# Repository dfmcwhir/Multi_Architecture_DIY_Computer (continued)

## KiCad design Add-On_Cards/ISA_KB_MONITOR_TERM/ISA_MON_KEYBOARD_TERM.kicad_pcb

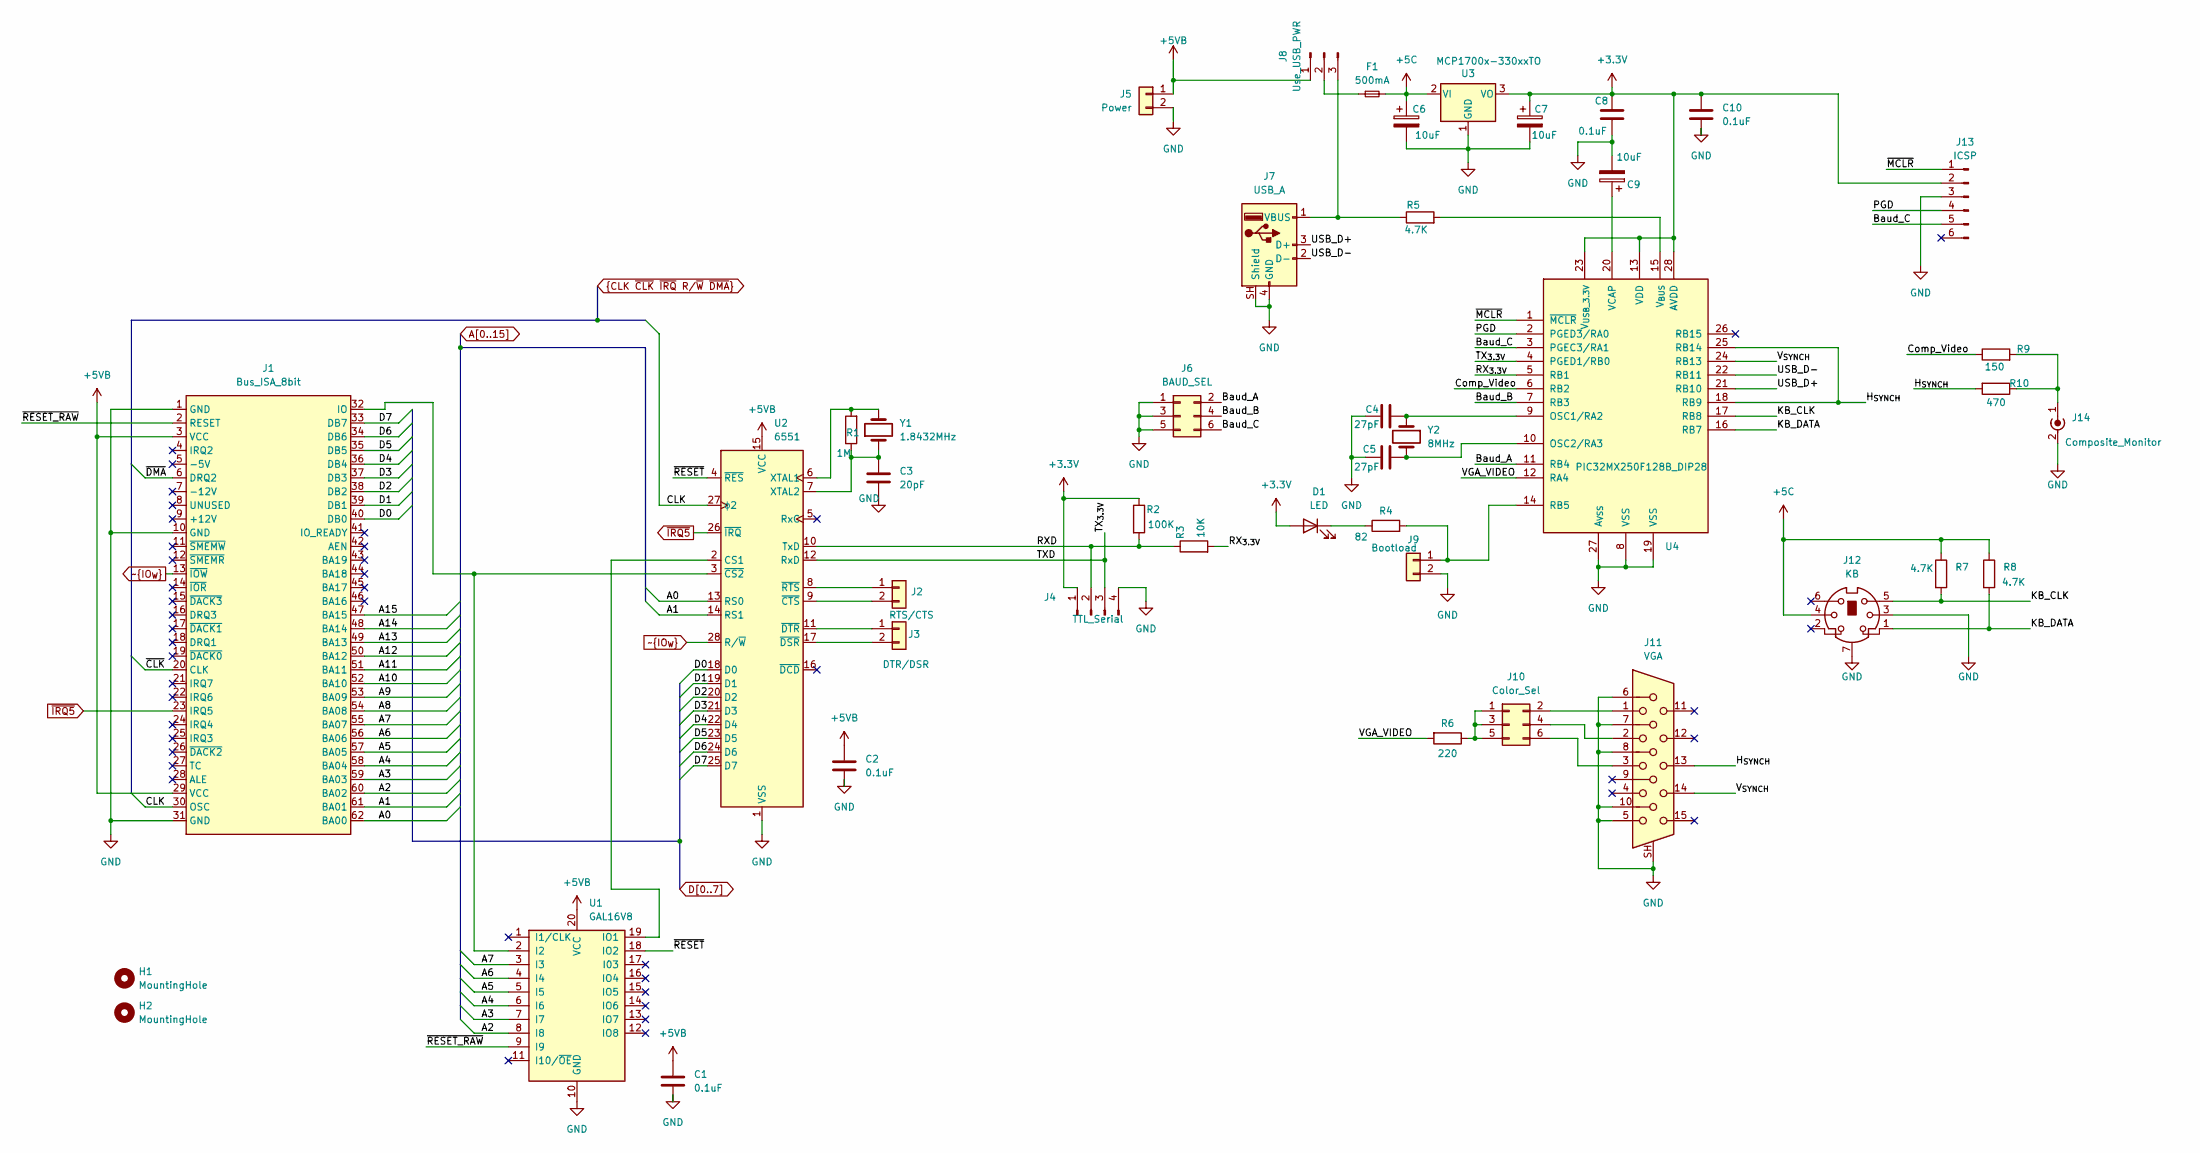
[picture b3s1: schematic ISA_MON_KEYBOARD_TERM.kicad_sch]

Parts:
C1, C2, C8, C10: 0.1uF; C_Disc_D4.7mm_W2.5mm_P5.00mm
C3: 20pF; C_Disc_D4.7mm_W2.5mm_P5.00mm
C4, C5: 27pF; C_Disc_D4.7mm_W2.5mm_P5.00mm
C6, C7, C9: 10uF; CP_Radial_D5.0mm_P2.50mm
D1: LED; LED_D5.0mm
F1: 500mA; R_Axial_DIN0207_L6.3mm_D2.5mm_P10.16mm_Horizontal
H1, H2: MountingHole; MountingHole_3.2mm_M3
J1: Bus_ISA_8bit; BUS_8-bit_ISA
J2: RTS/CTS; PinHeader_1x02_P2.54mm_Vertical
J3: DTR/DSR; PinHeader_1x02_P2.54mm_Vertical
J4: TTL_Serial; PinHeader_1x04_P2.54mm_Vertical
J5: Power; PinHeader_1x02_P2.54mm_Vertical
J6: BAUD_SEL; PinHeader_2x03_P2.54mm_Vertical
J7: USB_A; USB_A_Connfly_DS1095
J8: Use_USB_PWR; PinHeader_1x03_P2.54mm_Vertical
J9: Bootload; PinHeader_1x02_P2.54mm_Vertical
J10: Color_Sel; PinHeader_2x03_P2.54mm_Vertical
J11: VGA; DSUB-15-HD_Socket_Horizontal_P2.29x1.90mm_EdgePinOffset3.03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
J12: KB; Connector_Mini-DIN_Female_6Pin_2rows
J13: ICSP; PinHeader_1x06_P2.54mm_Vertical
J14: Composite_Monitor; RCA_JACK_Right_Angle_AliExpress
R1: 1M; R_Axial_DIN0207_L6.3mm_D2.5mm_P10.16mm_Horizontal
R2: 100K; R_Axial_DIN0207_L6.3mm_D2.5mm_P10.16mm_Horizontal
R3: 10K; R_Axial_DIN0207_L6.3mm_D2.5mm_P10.16mm_Horizontal
R4: 82; R_Axial_DIN0207_L6.3mm_D2.5mm_P10.16mm_Horizontal
R5, R7, R8: 4.7K; R_Axial_DIN0207_L6.3mm_D2.5mm_P10.16mm_Horizontal
R6: 220; R_Axial_DIN0207_L6.3mm_D2.5mm_P10.16mm_Horizontal
R9: 150; R_Axial_DIN0207_L6.3mm_D2.5mm_P10.16mm_Horizontal
R10: 470; R_Axial_DIN0207_L6.3mm_D2.5mm_P10.16mm_Horizontal
U1: GAL16V8; DIP-20_W7.62mm
U2: 6551; DIP-28_W15.24mm
U3: MCP1700x-330xxTO; TO-92_Wide
U4: PIC32MX250F128B_DIP28; DIP-28_W7.62mm
Y1: 1.8432MHz; Crystal_HC18-U_Vertical
Y2: 8MHz; Crystal_HC18-U_Vertical

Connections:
+3.3V: C7.1, C8.1, C10.1, D1.2 (A), J4.1, J13.2, R2.1, U3.3 (VO), U4.13 (VDD), U4.23 (V_{USB_3.3V}), U4.28 (AVDD)
+5C: C6.1, F1.2, J12.4, R7.1, R8.1, U3.2 (VI)
+5VB: C1.1, C2.1, J1.3 (VCC), J1.29 (VCC), J5.1, J8.1, U1.20 (VCC), U2.15 (VCC)
/Baud_A: J6.2, U4.11 (RB4)
/Baud_B: J6.4, U4.7 (RB3)
/Baud_C: J6.6, J13.5, U4.3 (PGEC3/RA1)
/Comp_Video: R9.1, U4.6 (RB2)
/H_{SYNCH}: J11.13, R10.2, U4.18 (RB9), U4.25 (RB14)
/KB_CLK: J12.5, R7.2, U4.17 (RB8)
/KB_DATA: J12.1, R8.2, U4.16 (RB7)
/PGD: J13.4, U4.2 (PGED3/RA0)
/RXD: J4.2, R2.2, R3.1, U2.10 (TxD)
/RX_{3.3V}: R3.2, U4.5 (RB1)
/TXD: J4.3, U2.12 (RxD), U4.4 (PGED1/RB0)
/USB_D+: J7.3 (D+), U4.21 (RB10)
/USB_D-: J7.2 (D-), U4.22 (RB11)
/VGA_VIDEO: R6.2, U4.12 (RA4)
/V_{SYNCH}: J11.14, U4.24 (RB13)
/~MCLR: J13.1, U4.1 (~MCLR)
/~RESET_RAW: J1.2 (RESET), U1.9 (I9)
/~RESET: U1.18 (IO2), U2.4 (~RES)
A0: J1.62 (BA00), U2.13 (RS0)
A1: J1.61 (BA01), U2.14 (RS1)
A2: J1.60 (BA02), U1.8 (I8)
A3: J1.59 (BA03), U1.7 (I7)
A4: J1.58 (BA04), U1.6 (I6)
A5: J1.57 (BA05), U1.5 (I5)
A6: J1.56 (BA06), U1.4 (I4)
A7: J1.55 (BA07), U1.3 (I3)
A8: J1.54 (BA08)
A9: J1.53 (BA09)
A10: J1.52 (BA10)
A11: J1.51 (BA11)
A12: J1.50 (BA12)
A13: J1.49 (BA13)
A14: J1.48 (BA14)
A15: J1.47 (BA15)
CLK: J1.30 (OSC), U2.27 (ϕ2)
D0: J1.40 (DB0), U2.18 (D0)
D1: J1.39 (DB1), U2.19 (D1)
D2: J1.38 (DB2), U2.20 (D2)
D3: J1.37 (DB3), U2.21 (D3)
D4: J1.36 (DB4), U2.22 (D4)
D5: J1.35 (DB5), U2.23 (D5)
D6: J1.34 (DB6), U2.24 (D6)
D7: J1.33 (DB7), U2.25 (D7)
GND: C1.2, C2.2, C3.2, C4.2, C5.2, C6.2, C7.2, C8.2, C9.2, C10.2, J1.1 (GND), J1.10 (GND), J1.31 (GND), J4.4, J5.2, J6.1, J6.3, J6.5, J7.4 (GND), J7.SH (Shield), J9.2, J11.5, J11.6, J11.7, J11.8, J11.10, J11.SH, J12.3, J12.7, J13.3, J14.2 (Ext), U1.10 (GND), U2.1 (VSS), U3.1 (GND), U4.8 (VSS), U4.19 (VSS), U4.27 (A_{VSS})
unnamed: D1.1 (K), R4.1
unnamed: J1.32 (IO), U1.2 (I2), U2.3 (~CS2)
unnamed: J2.1, U2.8 (~RTS)
unnamed: J2.2, U2.9 (~CTS)
unnamed: J3.1, U2.11 (~DTR)
unnamed: J3.2, U2.17 (~DSR)
unnamed: J7.1 (VBUS), J8.3, R5.1
unnamed: F1.1, J8.2
unnamed: J9.1, R4.2, U4.14 (RB5)
unnamed: J10.1, J10.3, J10.5, R6.1
unnamed: J10.2, J11.1
unnamed: J10.4, J11.2
unnamed: J10.6, J11.3
unnamed: J14.1 (In), R9.2, R10.1
unnamed: U1.19 (IO1), U2.2 (CS1)
unnamed: R1.2, U2.6 (XTAL1), Y1.2
unnamed: C3.1, R1.1, U2.7 (XTAL2), Y1.1
unnamed: C4.1, U4.9 (OSC1/RA2), Y2.1
unnamed: C5.1, U4.10 (OSC2/RA3), Y2.2
unnamed: C9.1, U4.20 (VCAP)
unnamed: R5.2, U4.15 (V_{BUS})
~CLK: J1.20 (CLK)
~DMA: J1.6 (DRQ2)
~IO_{W}: J1.13 (~IOW), U2.28 (R/~W)
~IRQ5: J1.23 (IRQ5), U2.26 (~IRQ)

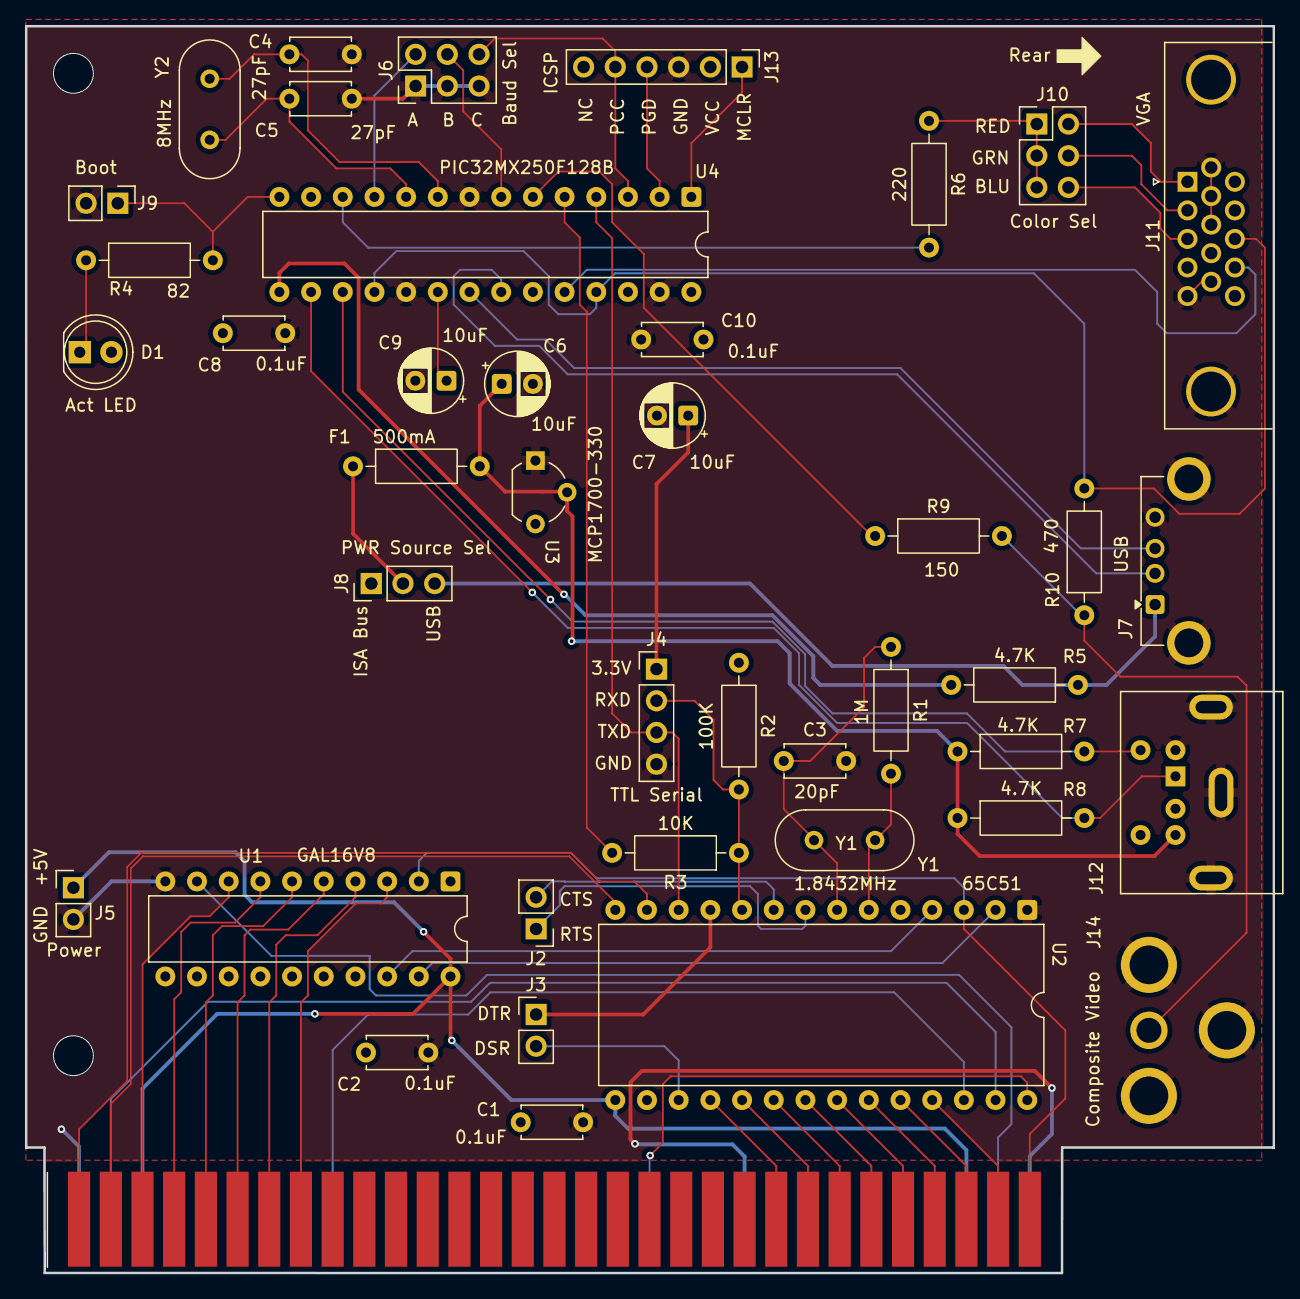
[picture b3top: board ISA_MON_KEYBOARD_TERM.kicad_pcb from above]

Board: 2 copper layers, 100.0 x 99.9 mm, 44 parts (0 on the bottom side), 62 nets.

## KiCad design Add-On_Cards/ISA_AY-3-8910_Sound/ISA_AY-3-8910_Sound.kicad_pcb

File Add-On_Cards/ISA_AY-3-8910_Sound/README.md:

<h2>AY-3-8910 sound card</h2>

<p>This a new card that hasn't been built or tested yet. However, a rev0 of the AY-3-8910 portion of this card was built and tested on a prototyping board and worked for sound. For this version of the card the I/O ports A and B were broken out and can be used for general purpose IO. The SPO256 speech chip was added to this version of the board as well.</p>

<h2>Known Bugs</h2>
<p>
  <li>Rev0 of this card ran fine at 2MHz, but to make this card capable of running at higher clock speeds, the PLD introduces a /WAIT signal. For the 6502_CPU_Rev2 card that means the J1 Wait_Sel jumper should be on pins 2-3. However, on the 8085 and Z80 cards that won't work. The current 8085 CPU card doesn't have the /WAIT or /STRETCH signals implemented at all. For the Z80 card both the /WAIT and /STRETCH signals stop the CLK, so the fix is to cut the trace to pin1 of the PLD and attach pin1 of the PLD to the TC (2XOSC) pin on the bus. That modification should also still work when using the 6502_CPU_Rev2 but with JP1 Wait_Sel set to pin 1-2. To make it work with the current 8085 card, it probably requires keeping the CPU speed <3MHz and updating the PLD to not use the /WAIT logic. My current 8085 card uses a 4.9152MHz crystal so the clock is ~2.45MHz, but I haven't tested it with the sound card yet. </li></p>

<h2>Resources</h2>
<table><thead><tr><th>Address</th><th>Function</th></tr></thead>
<tr><td>7F22</td><td>AY3 Command Register</td></tr>
<tr><td>7F23</td><td>AY3 Data Register</td></tr>
<tr><td>7F26</td><td>SPO256 command/status register</td></tr>
</table>

<p>The SPO256 can use IRQ7 but installing a jumper, but it isn't clear if that will be necessary or desirable.</p>

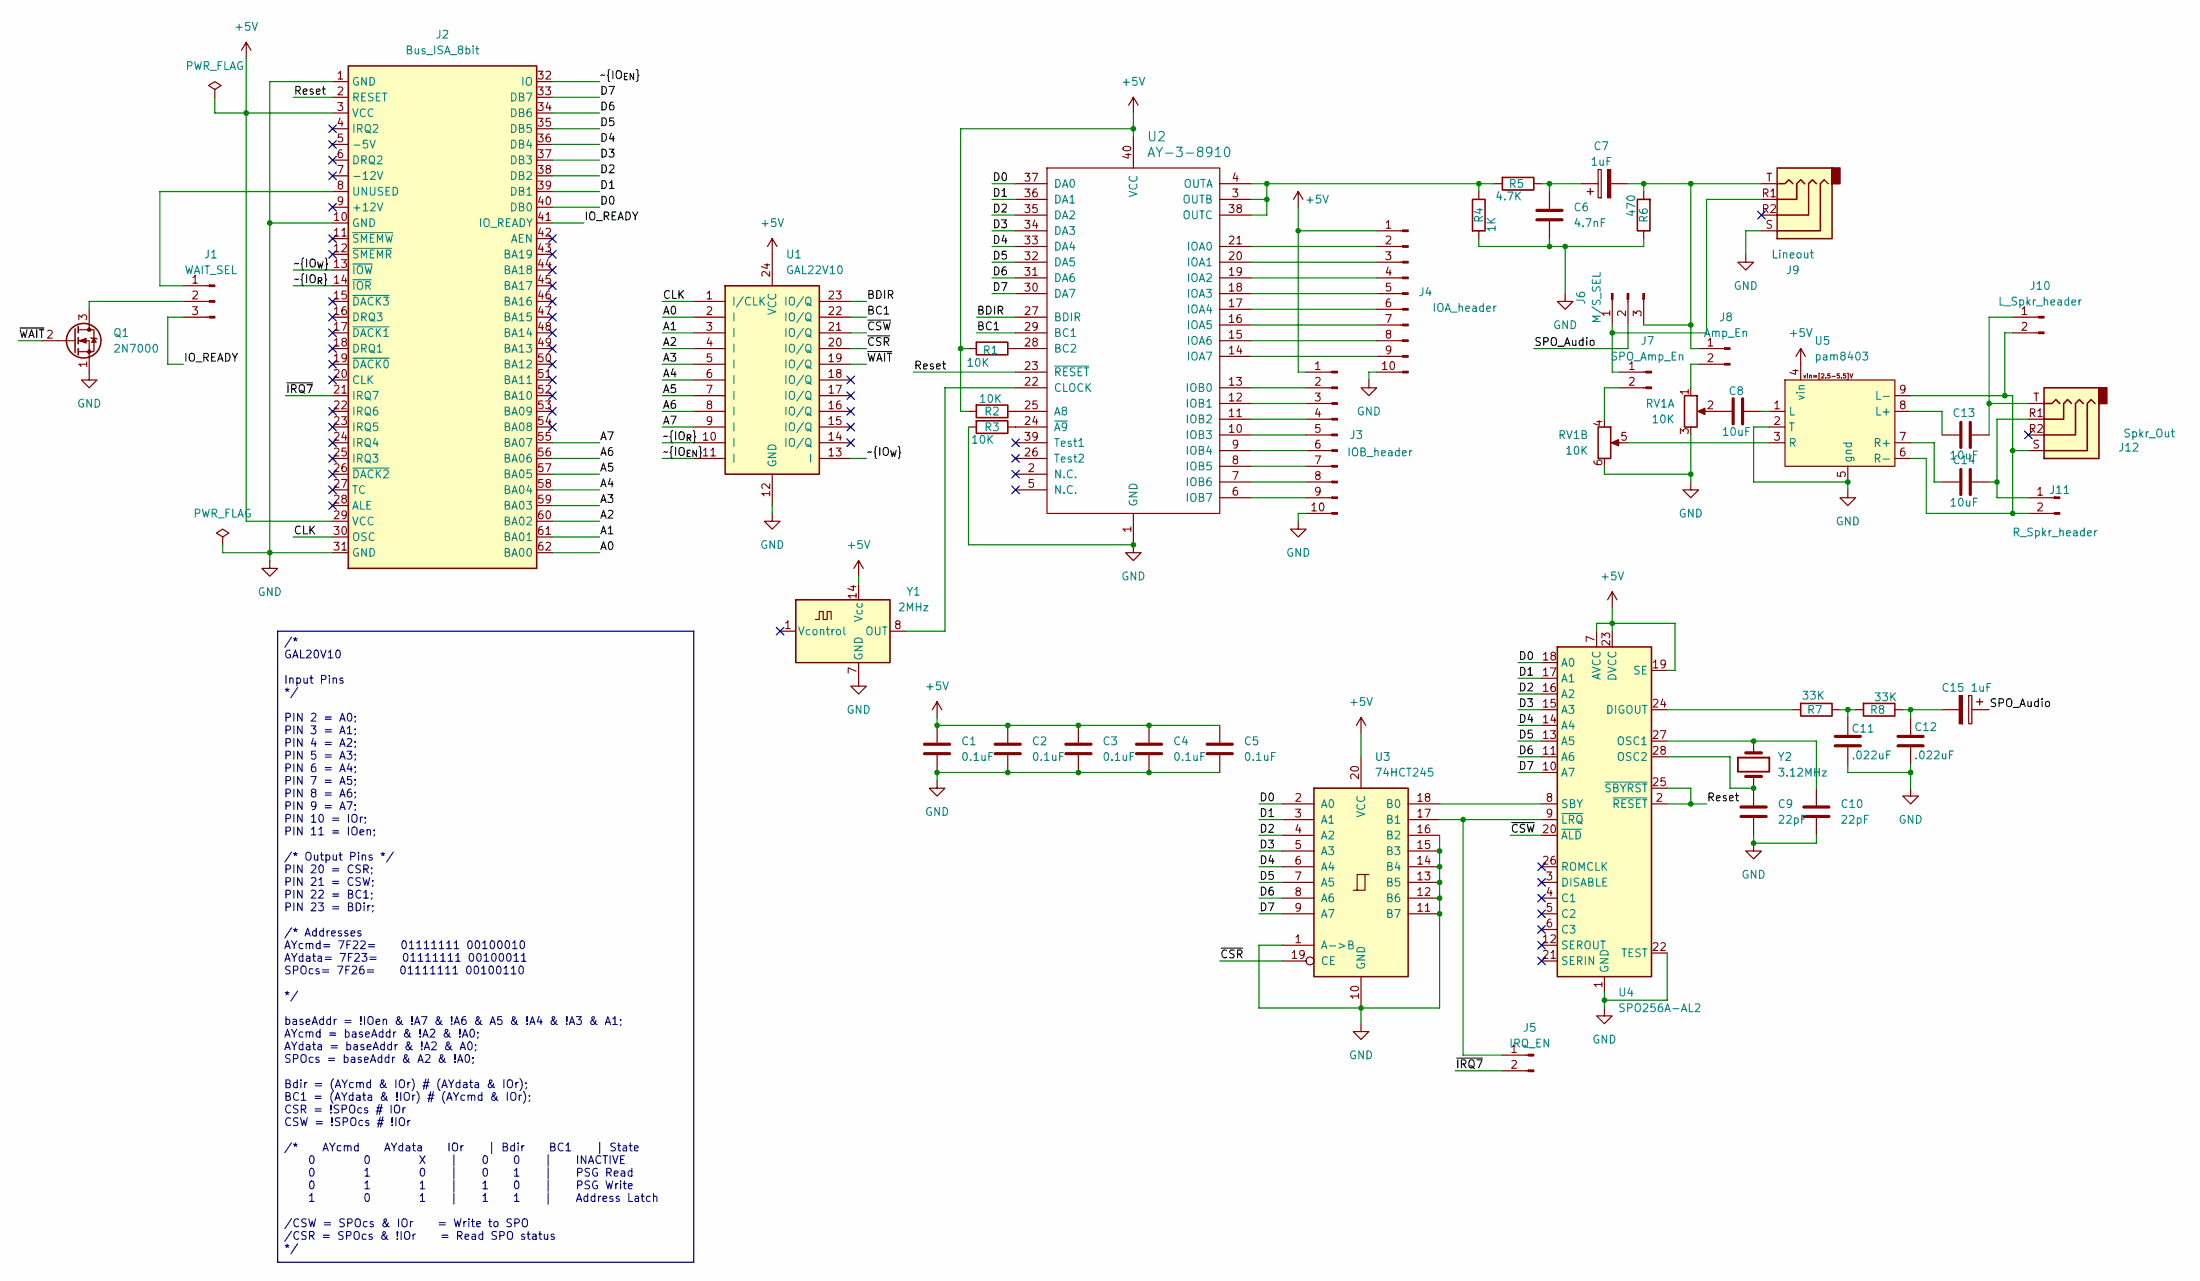
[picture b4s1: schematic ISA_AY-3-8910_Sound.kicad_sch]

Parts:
C1, C2, C3, C4, C5: 0.1uF; C_Disc_D4.7mm_W2.5mm_P5.00mm
C6: 4.7nF; C_Disc_D4.7mm_W2.5mm_P5.00mm
C7, C15: 1uF; CP_Radial_D6.3mm_P2.50mm
C8, C13, C14: 10uF; C_Disc_D4.7mm_W2.5mm_P5.00mm
C9, C10: 22pF; C_Disc_D4.7mm_W2.5mm_P5.00mm
C11, C12: .022uF; C_Disc_D4.7mm_W2.5mm_P5.00mm
J1: WAIT_SEL; PinHeader_1x03_P2.54mm_Vertical
J2: Bus_ISA_8bit; BUS_8-bit_ISA_CARD
J3: IOB_header; PinHeader_1x10_P2.54mm_Vertical
J4: IOA_header; PinHeader_1x10_P2.54mm_Vertical
J5: IRQ_EN; PinHeader_1x02_P2.54mm_Vertical
J6: M/S_SEL; PinHeader_1x03_P2.54mm_Vertical
J7: SPO_Amp_En; PinHeader_1x02_P2.54mm_Vertical
J8: Amp_En; PinHeader_1x02_P2.54mm_Vertical
J9: Lineout; Jack_3.5mm_PJ320E_Horizontal
J10: L_Spkr_header; PinHeader_1x02_P2.54mm_Vertical
J11: Spkr_Out; Jack_3.5mm_PJ320E_Horizontal
J12: R_Spkr_header; PinHeader_1x02_P2.54mm_Vertical
Q1: 2N7000; TO-92_Inline_Wide
R1, R2, R3: 10K; R_Axial_DIN0207_L6.3mm_D2.5mm_P10.16mm_Horizontal
R4: 1K; R_Axial_DIN0207_L6.3mm_D2.5mm_P10.16mm_Horizontal
R5: 4.7K; R_Axial_DIN0207_L6.3mm_D2.5mm_P10.16mm_Horizontal
R6: 470; R_Axial_DIN0207_L6.3mm_D2.5mm_P10.16mm_Horizontal
R7, R8: 33K; R_Axial_DIN0207_L6.3mm_D2.5mm_P10.16mm_Horizontal
RV1: 10K; Potentiometer_Alps_RK097_Dual_Horizontal
U1: GAL22V10; DIP-24_W7.62mm
U2: AY-3-8910; DIP-40_W15.24mm
U3: 74HCT245; DIP-20_W7.62mm
U4: SPO256A-AL2; DIP-28_W15.24mm
U5: pam8403
Y1: 2MHz; Oscillator_DIP-14
Y2: 3.12MHz; Crystal_HC18-U_Vertical

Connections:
+5V: C1.1, C2.1, C3.1, C4.1, C5.1, J2.3 (VCC), J2.29 (VCC), J3.1, J4.1, R1.2, R2.2, U1.24 (VCC), U2.40 (VCC), U3.20 (VCC), U4.7 (AVCC), U4.19 (SE), U4.23 (DVCC), U5.4 (vin), Y1.14 (Vcc)
/A0: J2.62 (BA00), U1.2 (I)
/A1: J2.61 (BA01), U1.3 (I)
/A2: J2.60 (BA02), U1.4 (I)
/A3: J2.59 (BA03), U1.5 (I)
/A4: J2.58 (BA04), U1.6 (I)
/A5: J2.57 (BA05), U1.7 (I)
/A6: J2.56 (BA06), U1.8 (I)
/A7: J2.55 (BA07), U1.9 (I)
/BC1: U1.22 (IO/Q), U2.29 (BC1)
/BDIR: U1.23 (IO/Q), U2.27 (BDIR)
/CLK: J2.30 (OSC), U1.1 (I/CLK)
/D0: J2.40 (DB0), U2.37 (DA0), U3.2 (A0), U4.18 (A0)
/D1: J2.39 (DB1), U2.36 (DA1), U3.3 (A1), U4.17 (A1)
/D2: J2.38 (DB2), U2.35 (DA2), U3.4 (A2), U4.16 (A2)
/D3: J2.37 (DB3), U2.34 (DA3), U3.5 (A3), U4.15 (A3)
/D4: J2.36 (DB4), U2.33 (DA4), U3.6 (A4), U4.14 (A4)
/D5: J2.35 (DB5), U2.32 (DA5), U3.7 (A5), U4.13 (A5)
/D6: J2.34 (DB6), U2.31 (DA6), U3.8 (A6), U4.11 (A6)
/D7: J2.33 (DB7), U2.30 (DA7), U3.9 (A7), U4.10 (A7)
/IO_READY: J1.3, J2.41 (IO_READY)
/Reset: J2.2 (RESET), U2.23 (~RESET), U4.2 (~RESET), U4.25 (~SBYRST)
/SPO_Audio: C15.1, J6.2
/~CSR: U1.20 (IO/Q), U3.19 (CE)
/~CSW: U1.21 (IO/Q), U4.20 (~ALD)
/~IO_{EN}: J2.32 (IO), U1.11 (I)
/~IO_{R}: J2.14 (~IOR), U1.10 (I)
/~IO_{W}: J2.13 (~IOW), U1.13 (I)
/~IRQ7: J2.21 (IRQ7), J5.2
/~WAIT: Q1.2 (G), U1.19 (IO/Q)
GND: C1.2, C2.2, C3.2, C4.2, C5.2, C6.2, C9.2, C10.2, C11.2, C12.2, J2.1 (GND), J2.10 (GND), J2.31 (GND), J3.10, J4.10, J9.S, Q1.1 (S), R3.2, R4.2, R6.1, RV1.3, RV1.6, U1.12 (GND), U2.1 (GND), U3.1 (A->B), U3.10 (GND), U3.11 (B7), U3.12 (B6), U3.13 (B5), U3.14 (B4), U3.15 (B3), U3.16 (B2), U4.1 (GND), U4.22 (TEST), U5.2 (T), U5.5 (gnd), Y1.7 (GND)
unnamed: C6.1, C7.1, R5.1
unnamed: C8.2, RV1.2
unnamed: C11.1, R7.1, R8.2
unnamed: C12.1, C15.2, R8.1
unnamed: J1.1, J2.8 (UNUSED)
unnamed: J1.2, Q1.3 (D)
unnamed: J3.2, U2.13 (IOB0)
unnamed: J3.3, U2.12 (IOB1)
unnamed: J3.4, U2.11 (IOB2)
unnamed: J3.5, U2.10 (IOB3)
unnamed: J3.6, U2.9 (IOB4)
unnamed: J3.7, U2.8 (IOB5)
unnamed: J3.8, U2.7 (IOB6)
unnamed: J3.9, U2.6 (IOB7)
unnamed: J4.2, U2.21 (IOA0)
unnamed: J4.3, U2.20 (IOA1)
unnamed: J4.4, U2.19 (IOA2)
unnamed: J4.5, U2.18 (IOA3)
unnamed: J4.6, U2.17 (IOA4)
unnamed: J4.7, U2.16 (IOA5)
unnamed: J4.8, U2.15 (IOA6)
unnamed: J4.9, U2.14 (IOA7)
unnamed: J5.1, U3.17 (B1), U4.9 (~LRQ)
unnamed: J6.1, J7.1, J9.R1
unnamed: C7.2, J6.3, J8.1, J9.T, R6.2
unnamed: J7.2, RV1.4
unnamed: J8.2, RV1.1
unnamed: C13.1, J10.1, J11.T
unnamed: J10.2, J11.S, J12.2, U5.6 (R-), U5.9 (L-)
unnamed: C14.1, J11.R1, J12.1
unnamed: R2.1, U2.25 (A8)
unnamed: R1.1, U2.28 (BC2)
unnamed: U2.22 (CLOCK), Y1.8 (OUT)
unnamed: R4.1, R5.2, U2.3 (OUTB), U2.4 (OUTA), U2.38 (OUTC)
unnamed: R3.1, U2.24 (~A9)
unnamed: U3.18 (B0), U4.8 (SBY)
unnamed: R7.2, U4.24 (DIGOUT)
unnamed: C10.1, U4.27 (OSC1), Y2.1
unnamed: C9.1, U4.28 (OSC2), Y2.2
unnamed: C8.1, U5.1 (L)
unnamed: C13.2, U5.8 (L+)
unnamed: RV1.5, U5.3 (R)
unnamed: C14.2, U5.7 (R+)

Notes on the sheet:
/* GAL20V10 Input Pins */ PIN 2 = A0; PIN 3 = A1; PIN 4 = A2; PIN 5 = A3; PIN 6 = A4; PIN 7 = A5; PIN 8 = A6; PIN 9 = A7; PIN 10 = IOr; PIN 11 = IOen; /* Output Pins */ PIN 20 = CSR; PIN 21 = CSW; PIN 22 = BC1; PIN 23 = BDir; /* Addresses AYcmd= 7F22= 01111111 00100010 AYdata= 7F23= 01111111 001000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

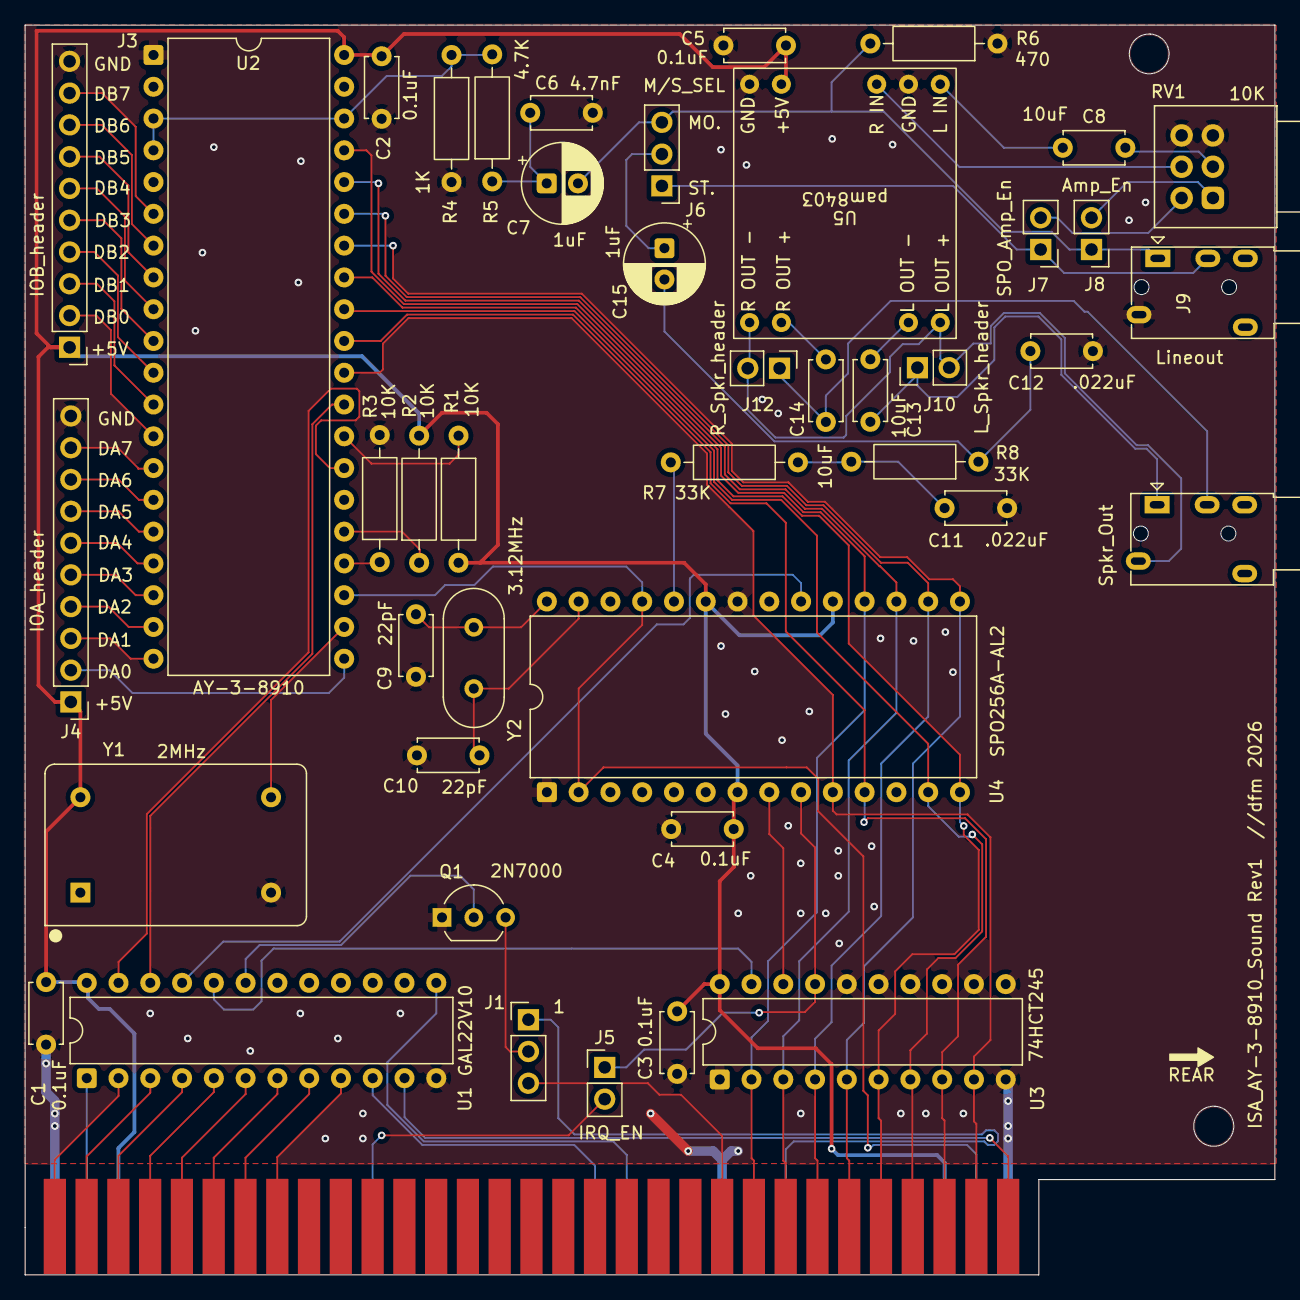
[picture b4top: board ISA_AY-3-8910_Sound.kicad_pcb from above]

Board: 2 copper layers, 99.9 x 99.9 mm, 44 parts (0 on the bottom side), 74 nets.

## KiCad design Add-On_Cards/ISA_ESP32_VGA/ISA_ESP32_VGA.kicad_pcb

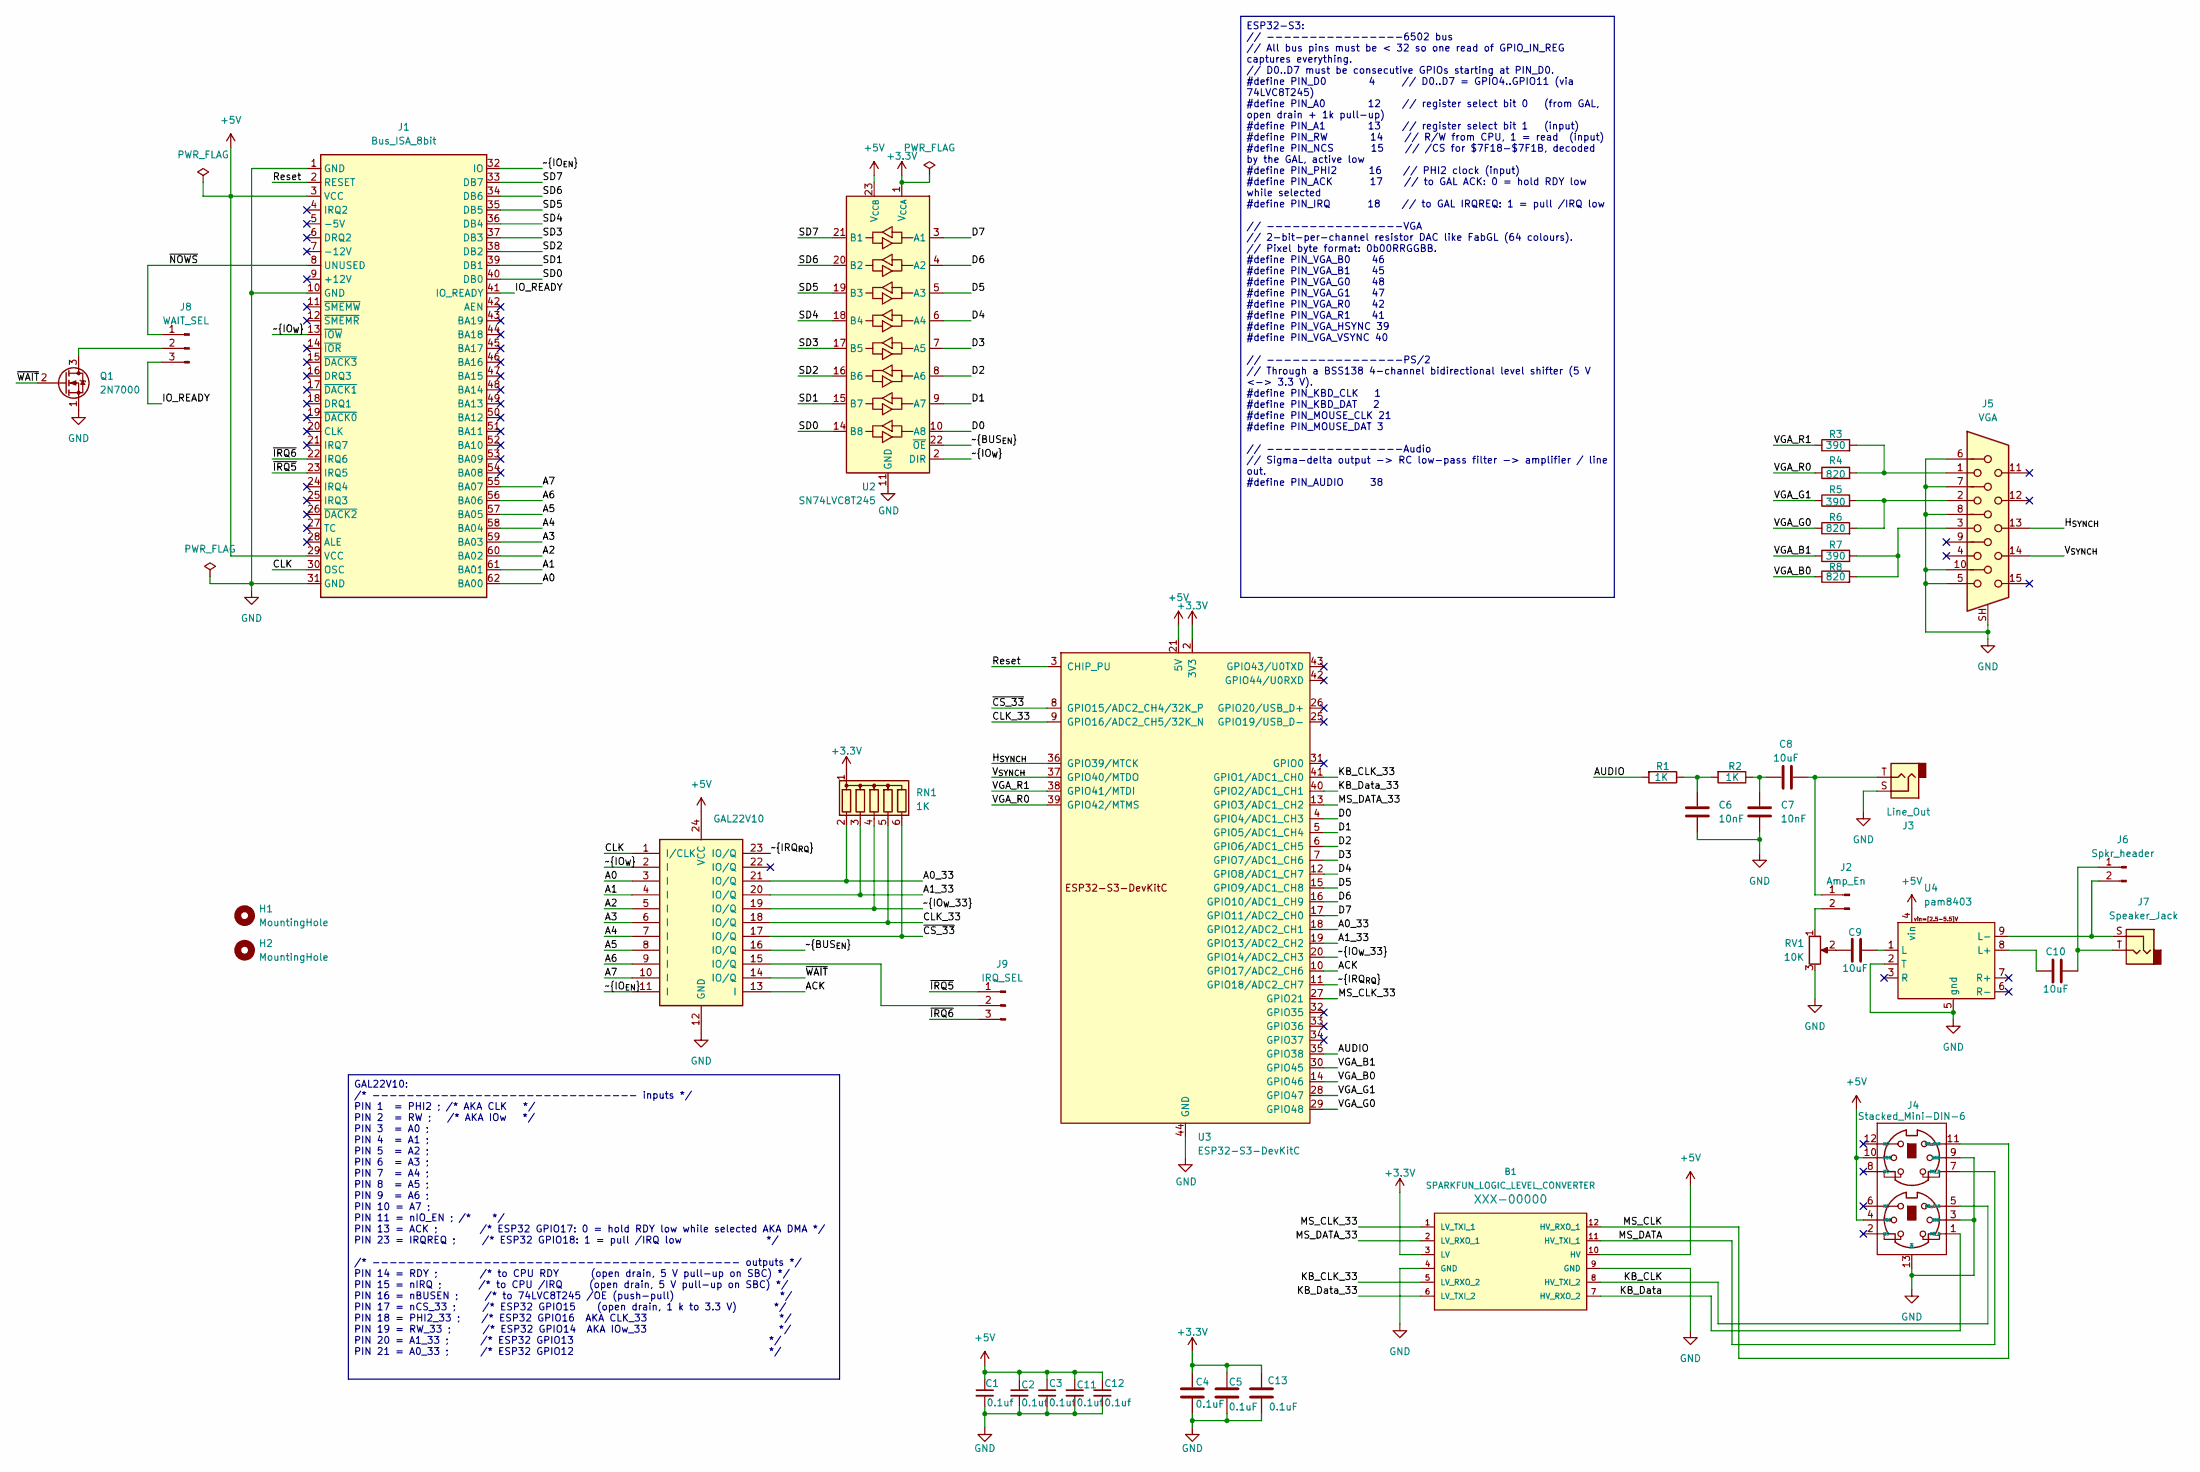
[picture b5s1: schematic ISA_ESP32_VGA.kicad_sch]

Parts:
B1: SPARKFUN_LOGIC_LEVEL_CONVERTER; 4_Chan_Logic_level_shifter_module
C1, C2, C3, C11, C12: 0.1uf; C_Disc_D4.7mm_W2.5mm_P5.00mm; Voltage 50V; Tolerance 5%
C4, C5, C13: 0.1uF; C_Disc_D4.7mm_W2.5mm_P5.00mm
C6, C7: 10nF; C_Disc_D4.7mm_W2.5mm_P5.00mm
C8, C9, C10: 10uF; C_Disc_D4.7mm_W2.5mm_P5.00mm
H1, H2: MountingHole; MountingHole_3.2mm_M3
J1: Bus_ISA_8bit; BUS_8-bit_ISA
J2: Amp_En; PinHeader_1x02_P2.54mm_Vertical
J3: Line_Out; Jack_3.5mm_PJ320E_Horizontal
J4: Stacked_Mini-DIN-6; Stacked_Mini-DIN_Female_6Pin_2rows
J5: VGA; DSUB-15-HD_Socket_Horizontal_P2.29x1.90mm_EdgePinOffset3.03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
J6: Spkr_header; PinHeader_1x02_P2.54mm_Vertical
J7: Speaker_Jack; Jack_3.5mm_PJ320E_Horizontal
J8: WAIT_SEL; PinHeader_1x03_P2.54mm_Vertical
J9: IRQ_SEL; PinHeader_1x03_P2.54mm_Vertical
Q1: 2N7000; TO-92_Inline_Wide
R1, R2: 1K; R_Axial_DIN0204_L3.6mm_D1.6mm_P5.08mm_Horizontal
R3, R5, R7: 390; R_Axial_DIN0204_L3.6mm_D1.6mm_P5.08mm_Horizontal
R4, R6, R8: 820; R_Axial_DIN0204_L3.6mm_D1.6mm_P5.08mm_Horizontal
RN1: 1K; R_Array_SIP6
RV1: 10K; Potentiometer_Alps_RK097_Dual_Horizontal
U1: GAL22V10; DIP-24_W7.62mm
U2: SN74LVC8T245; SOP-24_7.5x15.4mm_P1.27mm
U3: ESP32-S3-DevKitC; ESP32-S2-DevKitC-1
U4: pam8403

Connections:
+3.3V: B1.3 (LV), C4.1, C5.1, C13.1, RN1.1 (common), U2.1 (V_{CCA}), U3.1 (3V3), U3.2 (3V3)
+5V: B1.10 (HV), C1.1, C2.1, C3.1, C11.1, C12.1, J1.3 (VCC), J1.29 (VCC), J4.4 (VCC), J4.10 (VCC), U1.24 (VCC), U2.23 (V_{CCB}), U2.24 (V_{CCB}), U3.21 (5V), U4.4 (vin)
/A0: J1.62 (BA00), U1.3 (I)
/A0_33: RN1.2 (R1), U1.21 (IO/Q), U3.18 (GPIO12/ADC2_CH1)
/A1: J1.61 (BA01), U1.4 (I)
/A1_33: RN1.3 (R2), U1.20 (IO/Q), U3.19 (GPIO13/ADC2_CH2)
/A2: J1.60 (BA02), U1.5 (I)
/A3: J1.59 (BA03), U1.6 (I)
/A4: J1.58 (BA04), U1.7 (I)
/A5: J1.57 (BA05), U1.8 (I)
/A6: J1.56 (BA06), U1.9 (I)
/A7: J1.55 (BA07), U1.10 (I)
/ACK: U1.13 (I), U3.10 (GPIO17/ADC2_CH6)
/AUDIO: R1.2, U3.35 (GPIO38)
/CLK: J1.30 (OSC), U1.1 (I/CLK)
/CLK_33: RN1.5 (R4), U1.18 (IO/Q), U3.9 (GPIO16/ADC2_CH5/32K_N)
/D0: U2.10 (A8), U3.4 (GPIO4/ADC1_CH3)
/D1: U2.9 (A7), U3.5 (GPIO5/ADC1_CH4)
/D2: U2.8 (A6), U3.6 (GPIO6/ADC1_CH5)
/D3: U2.7 (A5), U3.7 (GPIO7/ADC1_CH6)
/D4: U2.6 (A4), U3.12 (GPIO8/ADC1_CH7)
/D5: U2.5 (A3), U3.15 (GPIO9/ADC1_CH8)
/D6: U2.4 (A2), U3.16 (GPIO10/ADC1_CH9)
/D7: U2.3 (A1), U3.17 (GPIO11/ADC2_CH0)
/H_{SYNCH}: J5.13, U3.36 (GPIO39/MTCK)
/IO_READY: J1.41 (IO_READY), J8.3
/KB_CLK: B1.8 (HV_TXI_2), J4.5 (KB_CLK)
/KB_CLK_33: B1.5 (LV_RXO_2), U3.41 (GPIO1/ADC1_CH0)
/KB_Data: B1.7 (HV_RXO_2), J4.1 (KB_D)
/KB_Data_33: B1.6 (LV_TXI_2), U3.40 (GPIO2/ADC1_CH1)
/MS_CLK: B1.12 (HV_RXO_1), J4.11 (MS_CLK)
/MS_CLK_33: B1.1 (LV_TXI_1), U3.27 (GPIO21)
/MS_DATA: B1.11 (HV_TXI_1), J4.7 (MS_D)
/MS_DATA_33: B1.2 (LV_RXO_1), U3.13 (GPIO3/ADC1_CH2)
/Reset: J1.2 (RESET), U3.3 (CHIP_PU)
/SD0: J1.40 (DB0), U2.14 (B8)
/SD1: J1.39 (DB1), U2.15 (B7)
/SD2: J1.38 (DB2), U2.16 (B6)
/SD3: J1.37 (DB3), U2.17 (B5)
/SD4: J1.36 (DB4), U2.18 (B4)
/SD5: J1.35 (DB5), U2.19 (B3)
/SD6: J1.34 (DB6), U2.20 (B2)
/SD7: J1.33 (DB7), U2.21 (B1)
/VGA_B0: R8.1, U3.14 (GPIO46)
/VGA_B1: R7.1, U3.30 (GPIO45)
/VGA_G0: R6.1, U3.29 (GPIO48)
/VGA_G1: R5.1, U3.28 (GPIO47)
/VGA_R0: R4.1, U3.39 (GPIO42/MTMS)
/VGA_R1: R3.1, U3.38 (GPIO41/MTDI)
/V_{SYNCH}: J5.14, U3.37 (GPIO40/MTDO)
/~BUS_{EN}: U1.16 (IO/Q), U2.22 (~OE)
/~CS_33: RN1.6 (R5), U1.17 (IO/Q), U3.8 (GPIO15/ADC2_CH4/32K_P)
/~IO_{EN}: J1.32 (IO), U1.11 (I)
/~IO_{W_33}: RN1.4 (R3), U1.19 (IO/Q), U3.20 (GPIO14/ADC2_CH3)
/~IO_{W}: J1.13 (~IOW), U1.2 (I), U2.2 (DIR)
/~IRQ5: J1.23 (IRQ5), J9.1
/~IRQ6: J1.22 (IRQ6), J9.3
/~IRQ_{RQ}: U1.23 (IO/Q), U3.11 (GPIO18/ADC2_CH7)
/~NOWS: J1.8 (UNUSED), J8.1
/~WAIT: Q1.2 (G), U1.14 (IO/Q)
GND: B1.4 (GND), B1.9 (GND), C1.2, C2.2, C3.2, C4.2, C5.2, C6.2, C7.2, C11.2, C12.2, C13.2, J1.1 (GND), J1.10 (GND), J1.31 (GND), J3.S, J4.3 (GND), J4.9 (GND), J4.13 (SH), J5.5, J5.6, J5.7, J5.8, J5.10, J5.SH, Q1.1 (S), RV1.3, U1.12 (GND), U2.11 (GND), U2.12 (GND), U2.13 (GND), U3.22 (GND), U3.23 (GND), U3.24 (GND), U3.44 (GND), U4.2 (T), U4.5 (gnd)
unnamed: C6.1, R1.1, R2.2
unnamed: C7.1, C8.1, R2.1
unnamed: C9.2, RV1.2
unnamed: C8.2, J2.1, J3.T
unnamed: J2.2, RV1.1
unnamed: J5.1, R3.2, R4.2
unnamed: J5.2, R5.2, R6.2
unnamed: J5.3, R7.2, R8.2
unnamed: C10.1, J6.1, J7.T
unnamed: J6.2, J7.S, U4.9 (L-)
unnamed: J8.2, Q1.3 (D)
unnamed: J9.2, U1.15 (IO/Q)
unnamed: C9.1, U4.1 (L)
unnamed: C10.2, U4.8 (L+)

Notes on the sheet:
ESP32-S3: // ----------------6502 bus // All bus pins must be < 32 so one read of GPIO_IN_REG captures everything. // D0..D7 must be consecutive GPIOs starting at PIN_D0. #define PIN_D0 4 // D0..D7 = GPIO4..GPIO11 (via 74LVC8T245) #define PIN_A0 12 // register select bit 0 (from GAL, open drain + 1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
GAL22V10: /* ------------------------------- inputs */ PIN 1 = PHI2 ; /* AKA CLK */ PIN 2 = RW ; /* AKA IOw */ PIN 3 = A0 ; PIN 4 = A1 ; PIN 5 = A2 ; PIN 6 = A3 ; PIN 7 = A4 ; PIN 8 = A5 ; PIN 9 = A6 ; PIN 10 = A7 ; PIN 11 = nIO_EN ; /* */ PIN 13 = ACK ; /* ESP32 GPIO17: 0 = hold RDY low while sele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

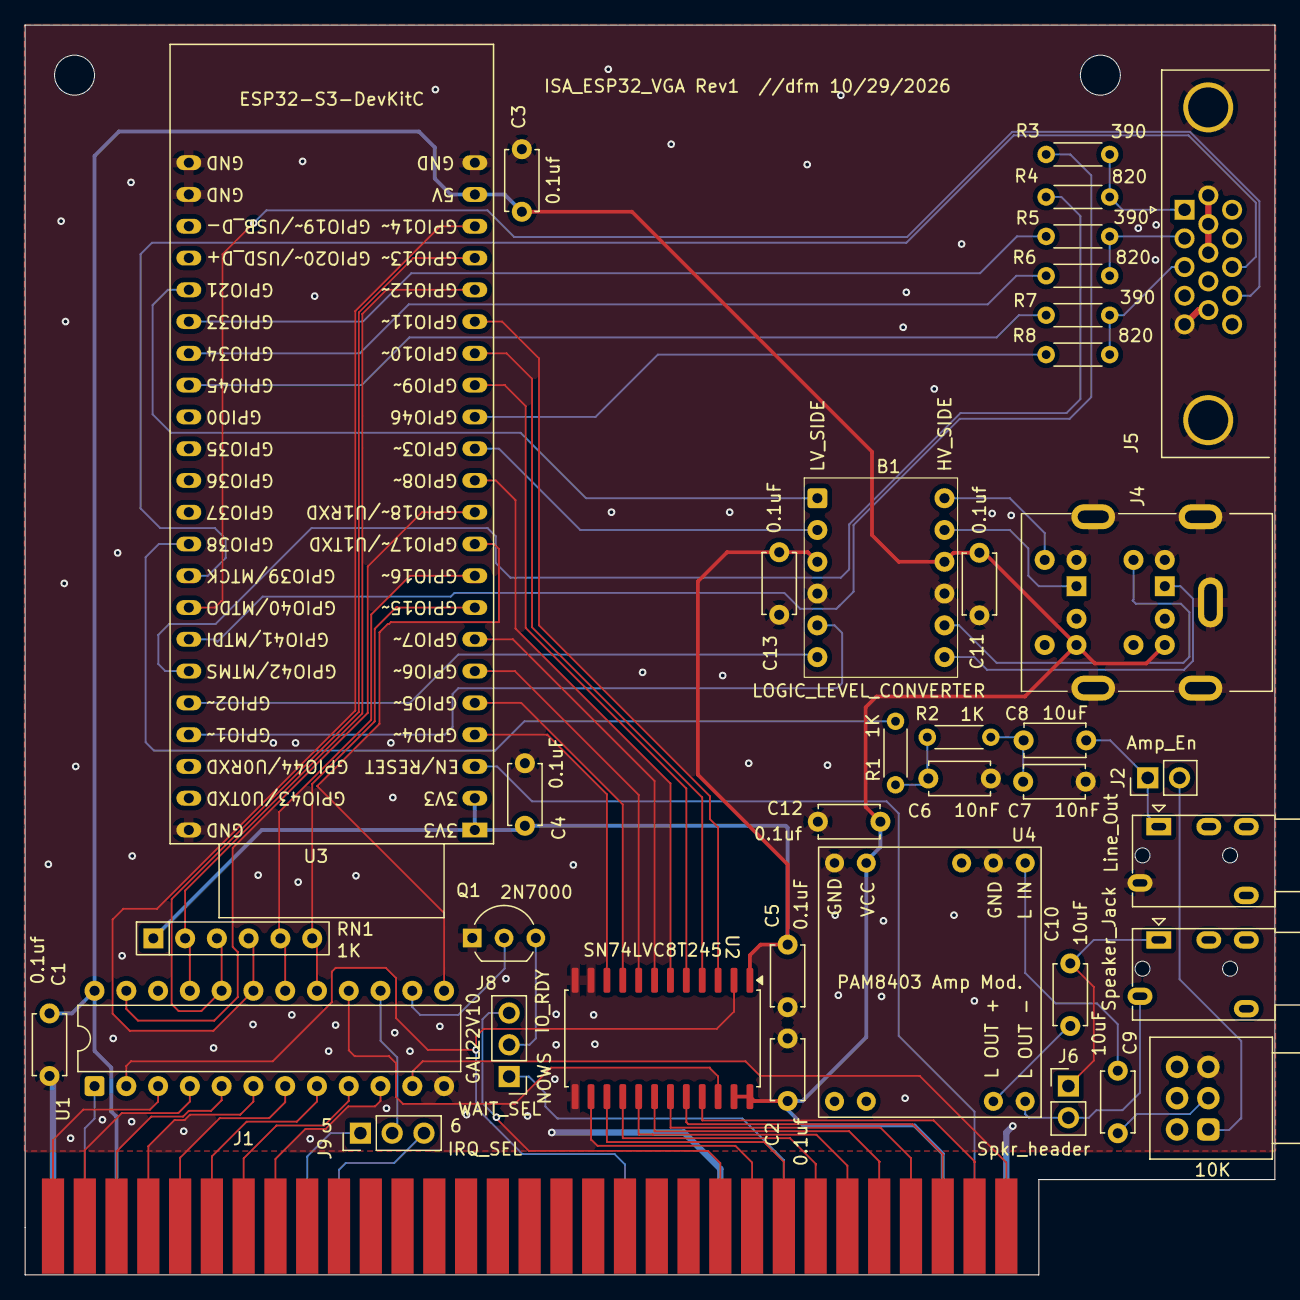
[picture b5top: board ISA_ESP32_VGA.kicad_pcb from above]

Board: 2 copper layers, 99.9 x 99.9 mm, 40 parts (0 on the bottom side), 75 nets.
